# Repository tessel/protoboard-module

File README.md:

protoboard-module
=================

Tessel module for quickly building DIY hardware modules.

Designs in KiCad.

### License

Copyright 2014 Technical Machine, Inc.

CC-BY-SA

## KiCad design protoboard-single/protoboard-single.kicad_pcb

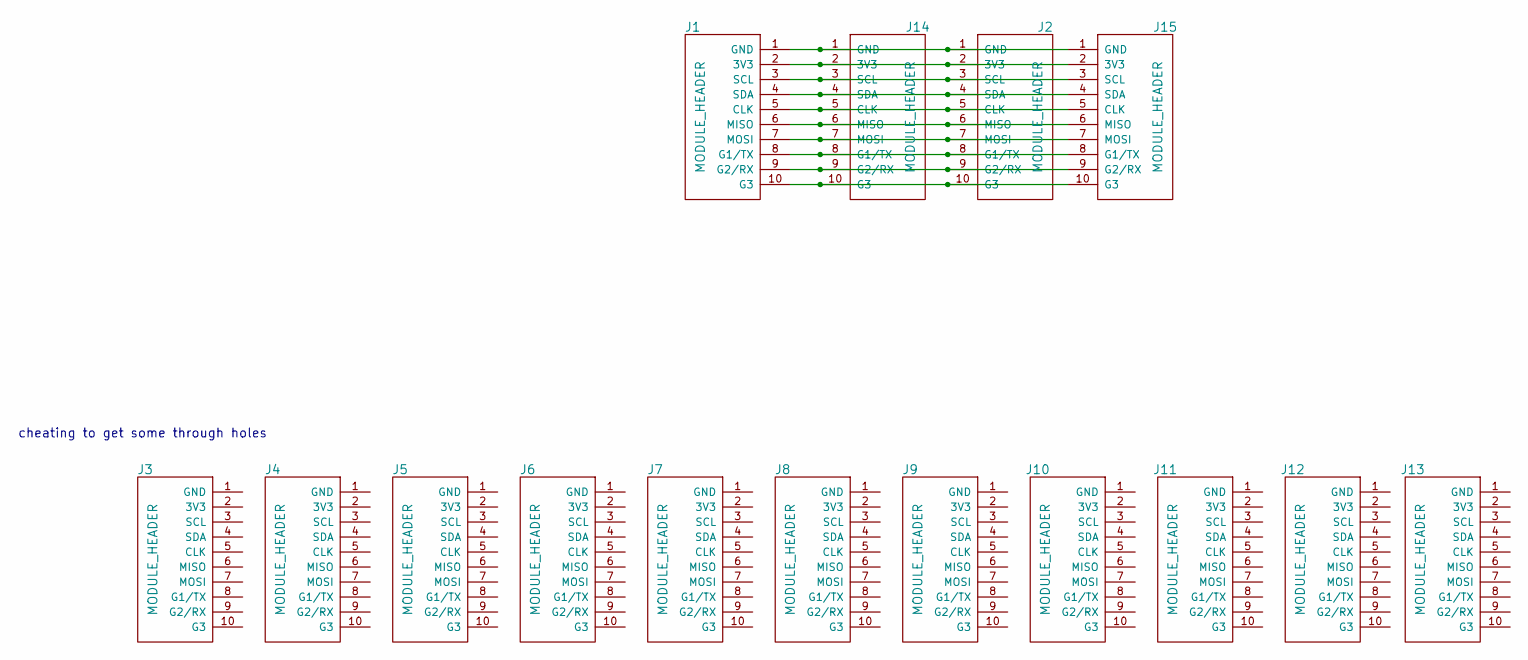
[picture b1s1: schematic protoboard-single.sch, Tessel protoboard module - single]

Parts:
J1: MODULE_HEADER; MODULE_HEADER_MODULE
J2, J3, J4, J5, J6, J7, J8, J9, J10, J11, J12, J13, J14, J15: MODULE_HEADER; 1x10

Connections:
unnamed: J1.1 (GND), J2.1 (GND), J14.1 (GND), J15.1 (GND)
unnamed: J1.2 (3V3), J2.2 (3V3), J14.2 (3V3), J15.2 (3V3)
unnamed: J1.3 (SCL), J2.3 (SCL), J14.3 (SCL), J15.3 (SCL)
unnamed: J1.4 (SDA), J2.4 (SDA), J14.4 (SDA), J15.4 (SDA)
unnamed: J1.5 (CLK), J2.5 (CLK), J14.5 (CLK), J15.5 (CLK)
unnamed: J1.6 (MISO), J2.6 (MISO), J14.6 (MISO), J15.6 (MISO)
unnamed: J1.7 (MOSI), J2.7 (MOSI), J14.7 (MOSI), J15.7 (MOSI)
unnamed: J1.8 (G1/TX), J2.8 (G1/TX), J14.8 (G1/TX), J15.8 (G1/TX)
unnamed: J1.9 (G2/RX), J2.9 (G2/RX), J14.9 (G2/RX), J15.9 (G2/RX)
unnamed: J1.10 (G3), J2.10 (G3), J14.10 (G3), J15.10 (G3)

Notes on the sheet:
cheating to get some through holes

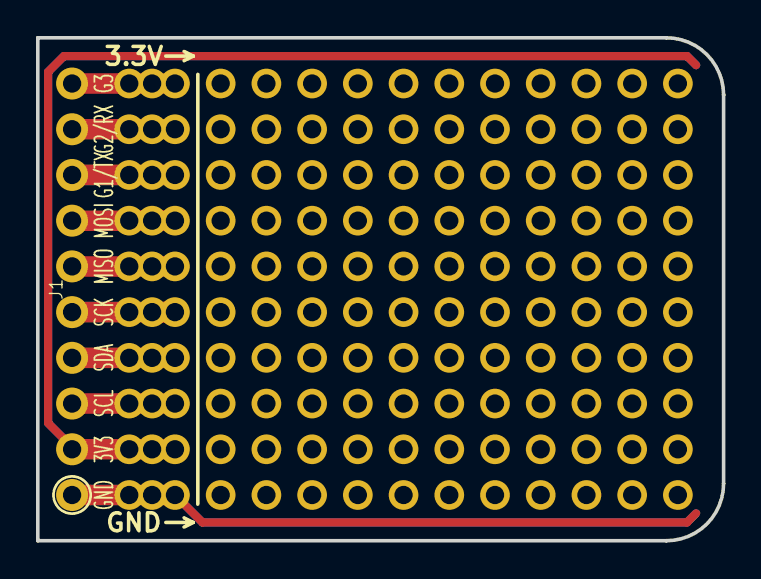
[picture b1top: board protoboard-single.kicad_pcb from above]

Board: 2 copper layers, 38.1 x 27.9 mm, 16 parts (1 on the bottom side), 10 nets.

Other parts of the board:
SILK1: logo; TESSEL-HEXAGON-LOGO-BACK

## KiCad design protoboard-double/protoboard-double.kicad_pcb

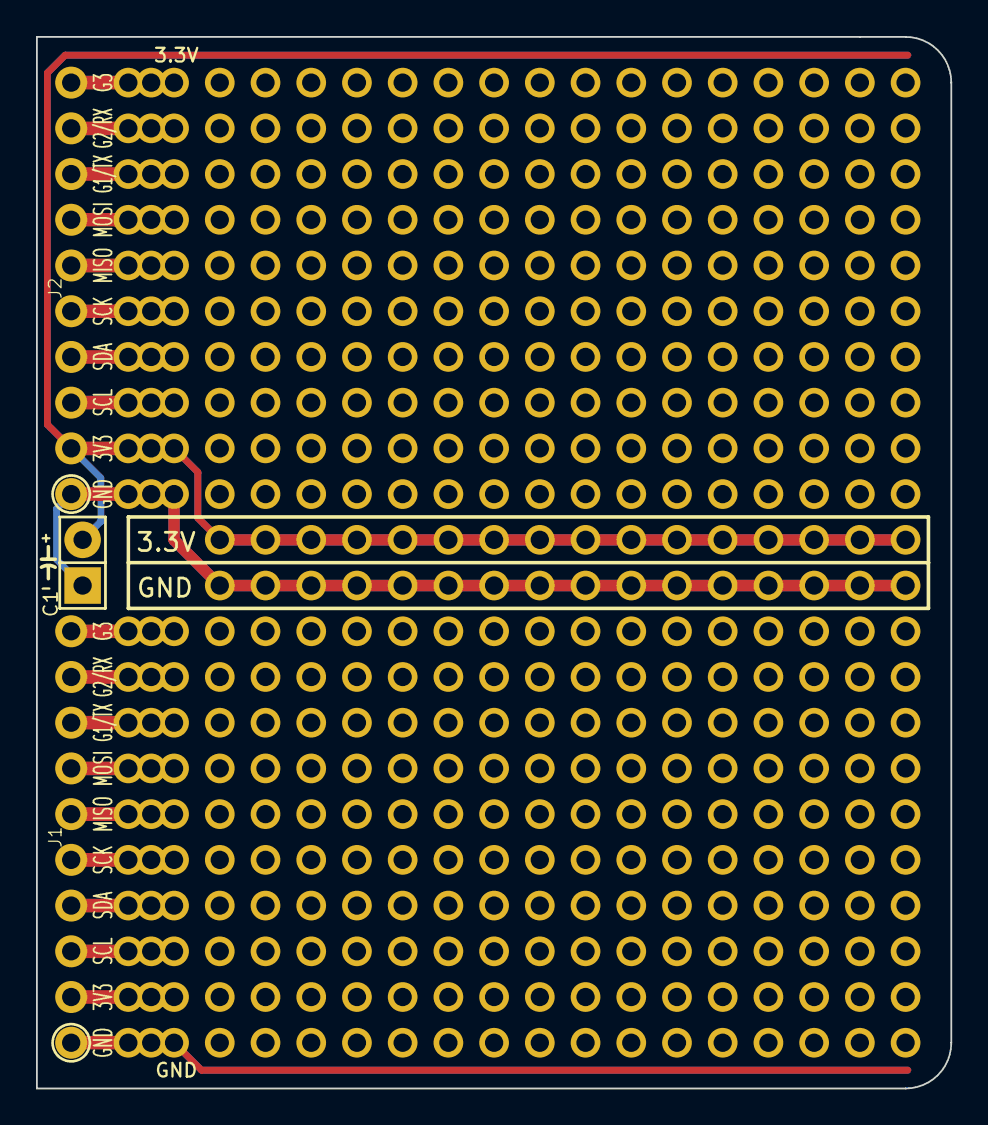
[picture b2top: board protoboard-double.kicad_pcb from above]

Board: 2 copper layers, 50.8 x 58.4 mm, 26 parts (1 on the bottom side), 20 nets.

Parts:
C1: C; Pin_Header_Straight_1x02
J1, J2: MODULE_HEADER; MODULE_HEADER_MODULE_BIG
P1, P2, P4, P5, P7, P8, P10, P11, P12, P13, P14, P15, P16, P17, P18, P19: CONN_01X22; 1x22_BIG
P3, P6, P9, P20, P21, P22: CONN_01X10; 1x10_BIG
SILK1: logo; TESSEL-HEXAGON-LOGO-BACK-BIG

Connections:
unnamed: C1.1, J2.1, P1.11, P2.11, P4.11, P5.11, P6.1, P7.11, P8.11, P10.11, P11.11, P12.11, P13.11, P14.11, P15.11, P16.11, P17.11, P18.11, P19.11, P20.1, P22.1
unnamed: C1.2, J2.2, P1.12, P2.12, P4.12, P5.12, P6.2, P7.12, P8.12, P10.12, P11.12, P12.12, P13.12, P14.12, P15.12, P16.12, P17.12, P18.12, P19.12, P20.2, P22.2
unnamed: J1.1, P3.1, P9.1, P21.1
unnamed: J1.2, P3.2, P9.2, P21.2
unnamed: J1.3, P3.3, P9.3, P21.3
unnamed: J1.4, P3.4, P9.4, P21.4
unnamed: J1.5, P3.5, P9.5, P21.5
unnamed: J1.6, P3.6, P9.6, P21.6
unnamed: J1.7, P3.7, P9.7, P21.7
unnamed: J1.8, P3.8, P9.8, P21.8
unnamed: J1.9, P3.9, P9.9, P21.9
unnamed: J1.10, P3.10, P9.10, P21.10
unnamed: J2.3, P6.3, P20.3, P22.3
unnamed: J2.4, P6.4, P20.4, P22.4
unnamed: J2.5, P6.5, P20.5, P22.5
unnamed: J2.6, P6.6, P20.6, P22.6
unnamed: J2.7, P6.7, P20.7, P22.7
unnamed: J2.8, P6.8, P20.8, P22.8
unnamed: J2.9, P6.9, P20.9, P22.9
unnamed: J2.10, P6.10, P20.10, P22.10

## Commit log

2014-09-09 license
2014-09-09 carriage returns in markdown...
2014-09-09 first pass shcem and board outline
2014-09-09 more access to each signal
2014-09-09 ship it
2014-09-09 moved j1 refdes
2014-09-09 gerbers, zip thereof
2014-09-09 close, save project and head home
2014-10-16 schem, netlist, component map for doublewide
2014-10-16 so there goes the layot
2014-10-16 gerbers and zip
2014-10-16 saved, closed project
2014-10-17 production-ready files?
2014-10-17 doublewide ready for production
2014-10-21 rezip
2014-10-23 rezip for fab
2014-11-03 user feedback incorporated for single
2014-11-04 feedback incorporated for doublewide. all aboard the PCB ship!
